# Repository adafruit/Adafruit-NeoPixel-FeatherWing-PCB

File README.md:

## Adafruit NeoPixel FeatherWing PCB
<a href="http://www.adafruit.com/products/2945"><br/>
Click here to purchase one from the Adafruit shop</a>

This is the NeoPixel FeatherWing, a 4x8 RGB LED Add-on For All Feather Boards! Using our Feather Stacking Headers or Feather Female Headers you can connect a FeatherWing on top or bottom of your Feather board and make your Feather board strut like a peacock at a rave.

Put on your sunglasses before staring into these 32 configurable eye-blistering RGB LEDs. Arranged in a 4x8 matrix, each pixel is individually addressable. Only one pin is required to control all the LEDs. On the bottom we have jumpers for the DIN line to any of the I/O pins on a Feather.  Works with any/all of our Feathers! You can cut the default jumper trace and use any pin you like. (In particular, the default pin for Feather Huzzah ESP8266 must be moved, try pin #15!) It works with but is not recommended for ESP32 Feather at this time due to a NeoPixel timing issue that makes it hard to control more than 30 pixels

PCB files for the Adafruit NeoPixel FeatherWing. The format is EagleCAD schematic and board layout
- http://www.adafruit.com/products/2945

### License

Adafruit invests time and resources providing this open source design, please support Adafruit and open-source hardware by purchasing products from [Adafruit](https://www.adafruit.com)!

All text above must be included in any redistribution

Designed by Limor Fried/Ladyada for Adafruit Industries.
Creative Commons Attribution/Share-Alike, all text above must be included in any redistribution. 
See license.txt for additional information.

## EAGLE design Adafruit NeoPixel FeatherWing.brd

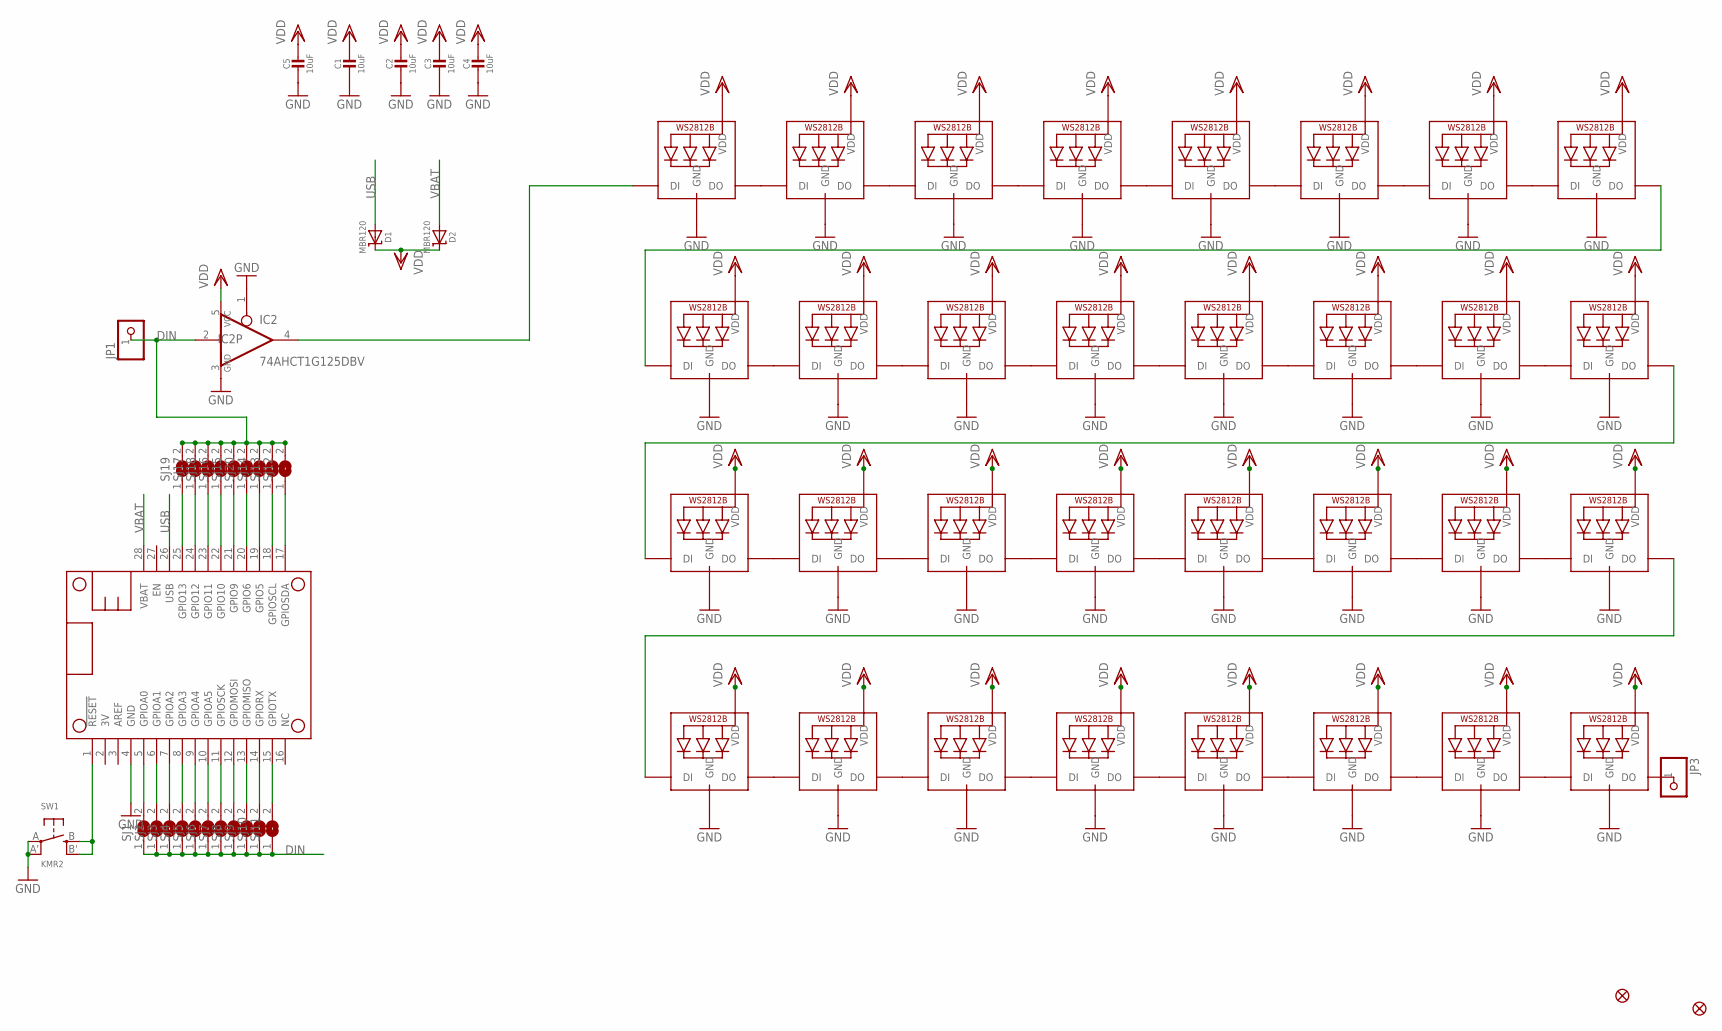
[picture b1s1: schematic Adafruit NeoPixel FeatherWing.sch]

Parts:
C1, C2, C3, C4, C5: 10uF; 0805-NO
D1, D2: MBR120; SOD-123
FID1, FID3: FIDUCIAL""; FIDUCIAL_1MM
IC2: 74AHCT1G125DBV; SOT23-5
JP1, JP3: HEADER-1X1ROUND; 1X01_ROUND
LED1, LED2, LED3, LED4, LED5, LED6, LED7, LED8, LED9, LED10, LED11, LED12, LED13, LED14, LED15, LED16, LED17, LED18, LED19, LED20, LED21, LED22, LED23, LED24, LED25, LED26, LED27, LED28, LED29, LED30, LED31, LED32: WS2812B3535; LED3535
MS1: FEATHERWING
SJ1, SJ2, SJ3, SJ4, SJ5, SJ6, SJ7, SJ8, SJ9, SJ10, SJ11, SJ12, SJ13, SJ14, SJ15, SJ16, SJ17, SJ18, SJ19: SOLDERJUMPER; SOLDERJUMPER_ARROW_NOPASTE
SJ20: SOLDERJUMPERCLOSED; SOLDERJUMPER_CLOSEDWIRE
SW1: KMR2; BTN_KMR2_4.6X2.8

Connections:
D6: MS1.20 (GPIO6), SJ20.1
DIN: IC2.2 (I), JP1.1, SJ1.1, SJ2.1, SJ3.1, SJ4.1, SJ5.1, SJ6.1, SJ7.1, SJ8.1, SJ9.1, SJ10.1, SJ11.1, SJ12.2, SJ13.2, SJ14.2, SJ15.2, SJ16.2, SJ17.2, SJ18.2, SJ19.2, SJ20.2
GND: C1.2, C2.2, C3.2, C4.2, C5.2, IC2.1 (OE), IC2.3 (GND), LED1.4 (GND), LED2.4 (GND), LED3.4 (GND), LED4.4 (GND), LED5.4 (GND), LED6.4 (GND), LED7.4 (GND), LED8.4 (GND), LED9.4 (GND), LED10.4 (GND), LED11.4 (GND), LED12.4 (GND), LED13.4 (GND), LED14.4 (GND), LED15.4 (GND), LED16.4 (GND), LED17.4 (GND), LED18.4 (GND), LED19.4 (GND), LED20.4 (GND), LED21.4 (GND), LED22.4 (GND), LED23.4 (GND), LED24.4 (GND), LED25.4 (GND), LED26.4 (GND), LED27.4 (GND), LED28.4 (GND), LED29.4 (GND), LED30.4 (GND), LED31.4 (GND), LED32.4 (GND), MS1.4 (GND), SW1.A, SW1.A' (P1)
unnamed: LED19.3 (DO), LED20.1 (DI)
unnamed: LED20.3 (DO), LED21.1 (DI)
unnamed: MS1.25 (GPIO13), SJ19.1
unnamed: MS1.15 (GPIOTX), SJ11.2
unnamed: MS1.24 (GPIO12), SJ17.1
unnamed: MS1.14 (GPIORX), SJ10.2
unnamed: MS1.13 (GPIOMISO), SJ9.2
unnamed: MS1.12 (GPIOMOSI), SJ8.2
unnamed: MS1.11 (GPIOSCK), SJ7.2
unnamed: MS1.10 (GPIOA5), SJ6.2
unnamed: MS1.9 (GPIOA4), SJ5.2
unnamed: MS1.8 (GPIOA3), SJ4.2
unnamed: MS1.7 (GPIOA2), SJ3.2
unnamed: MS1.6 (GPIOA1), SJ2.2
unnamed: MS1.5 (GPIOA0), SJ1.2
unnamed: LED6.3 (DO), LED25.1 (DI)
unnamed: LED21.3 (DO), LED22.1 (DI)
unnamed: MS1.1 (!RESET), SW1.B (S), SW1.B' (S1)
unnamed: MS1.23 (GPIO11), SJ18.1
unnamed: MS1.22 (GPIO10), SJ16.1
unnamed: MS1.21 (GPIO9), SJ15.1
unnamed: IC2.4 (O), LED1.1 (DI)
unnamed: MS1.19 (GPIO5), SJ14.1
unnamed: MS1.18 (GPIOSCL), SJ13.1
unnamed: MS1.17 (GPIOSDA), SJ12.1
unnamed: LED1.3 (DO), LED2.1 (DI)
unnamed: LED2.3 (DO), LED3.1 (DI)
unnamed: LED3.3 (DO), LED4.1 (DI)
unnamed: LED4.3 (DO), LED5.1 (DI)
unnamed: LED5.3 (DO), LED6.1 (DI)
unnamed: LED7.3 (DO), LED8.1 (DI)
unnamed: LED8.3 (DO), LED9.1 (DI)
unnamed: LED9.3 (DO), LED10.1 (DI)
unnamed: LED10.3 (DO), LED11.1 (DI)
unnamed: LED11.3 (DO), LED12.1 (DI)
unnamed: LED13.3 (DO), LED14.1 (DI)
unnamed: LED14.3 (DO), LED15.1 (DI)
unnamed: LED15.3 (DO), LED16.1 (DI)
unnamed: LED16.3 (DO), LED17.1 (DI)
unnamed: LED17.3 (DO), LED18.1 (DI)
unnamed: LED12.3 (DO), LED27.1 (DI)
unnamed: LED7.1 (DI), LED26.3 (DO)
unnamed: LED22.3 (DO), LED23.1 (DI)
unnamed: LED23.3 (DO), LED24.1 (DI)
unnamed: LED19.1 (DI), LED30.3 (DO)
unnamed: LED24.3 (DO), LED31.1 (DI)
unnamed: LED25.3 (DO), LED26.1 (DI)
unnamed: LED27.3 (DO), LED28.1 (DI)
unnamed: LED18.3 (DO), LED29.1 (DI)
unnamed: LED29.3 (DO), LED30.1 (DI)
unnamed: LED31.3 (DO), LED32.1 (DI)
unnamed: JP3.1, LED32.3 (DO)
unnamed: LED13.1 (DI), LED28.3 (DO)
USB: D1.A, MS1.26 (USB)
VBAT: D2.A, MS1.28 (VBAT)
VDD: C1.1, C2.1, C3.1, C4.1, C5.1, D1.C, D2.C, IC2.5 (VCC), LED1.2 (VDD), LED2.2 (VDD), LED3.2 (VDD), LED4.2 (VDD), LED5.2 (VDD), LED6.2 (VDD), LED7.2 (VDD), LED8.2 (VDD), LED9.2 (VDD), LED10.2 (VDD), LED11.2 (VDD), LED12.2 (VDD), LED13.2 (VDD), LED14.2 (VDD), LED15.2 (VDD), LED16.2 (VDD), LED17.2 (VDD), LED18.2 (VDD), LED19.2 (VDD), LED20.2 (VDD), LED21.2 (VDD), LED22.2 (VDD), LED23.2 (VDD), LED24.2 (VDD), LED25.2 (VDD), LED26.2 (VDD), LED27.2 (VDD), LED28.2 (VDD), LED29.2 (VDD), LED30.2 (VDD), LED31.2 (VDD), LED32.2 (VDD)

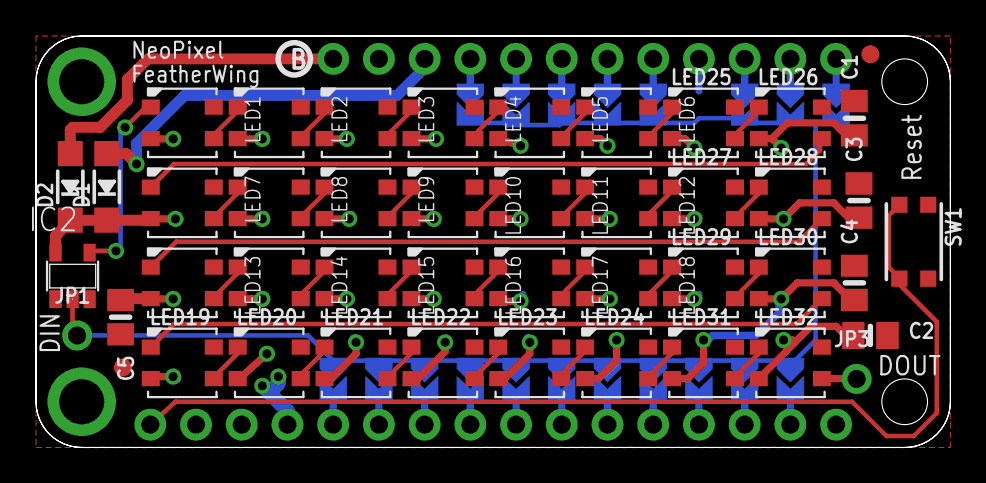
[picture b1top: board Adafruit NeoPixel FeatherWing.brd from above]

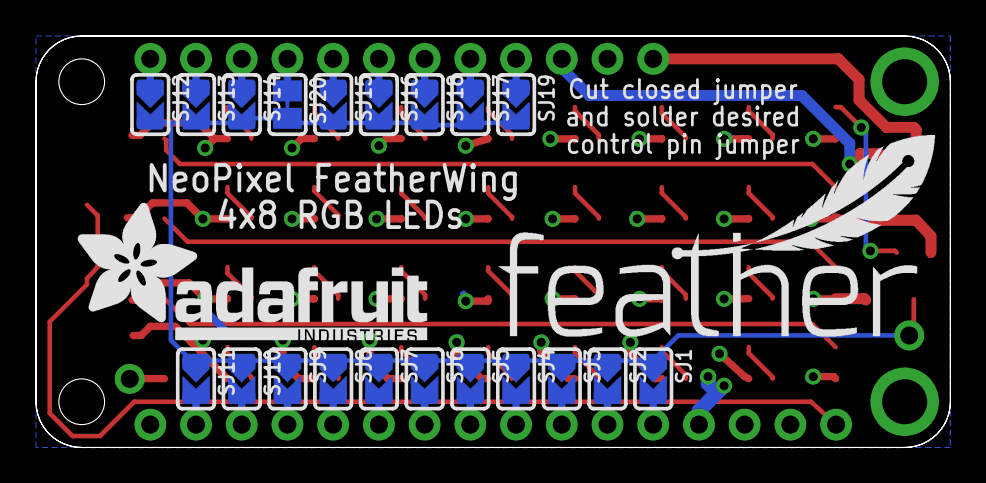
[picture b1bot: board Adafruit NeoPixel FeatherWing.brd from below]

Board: 2 copper layers, 50.8 x 22.9 mm, 69 parts (22 on the bottom side), 59 nets.

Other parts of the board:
U$2: PCBFEAT-REV-040
U$3: FEATHERLOGO
U$4: ADAFRUIT_TEXT_20MM

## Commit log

2016-06-20 neo-init
